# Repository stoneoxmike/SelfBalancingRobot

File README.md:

Self Balancing Robot
To this point, we have stolen EVERYTHING

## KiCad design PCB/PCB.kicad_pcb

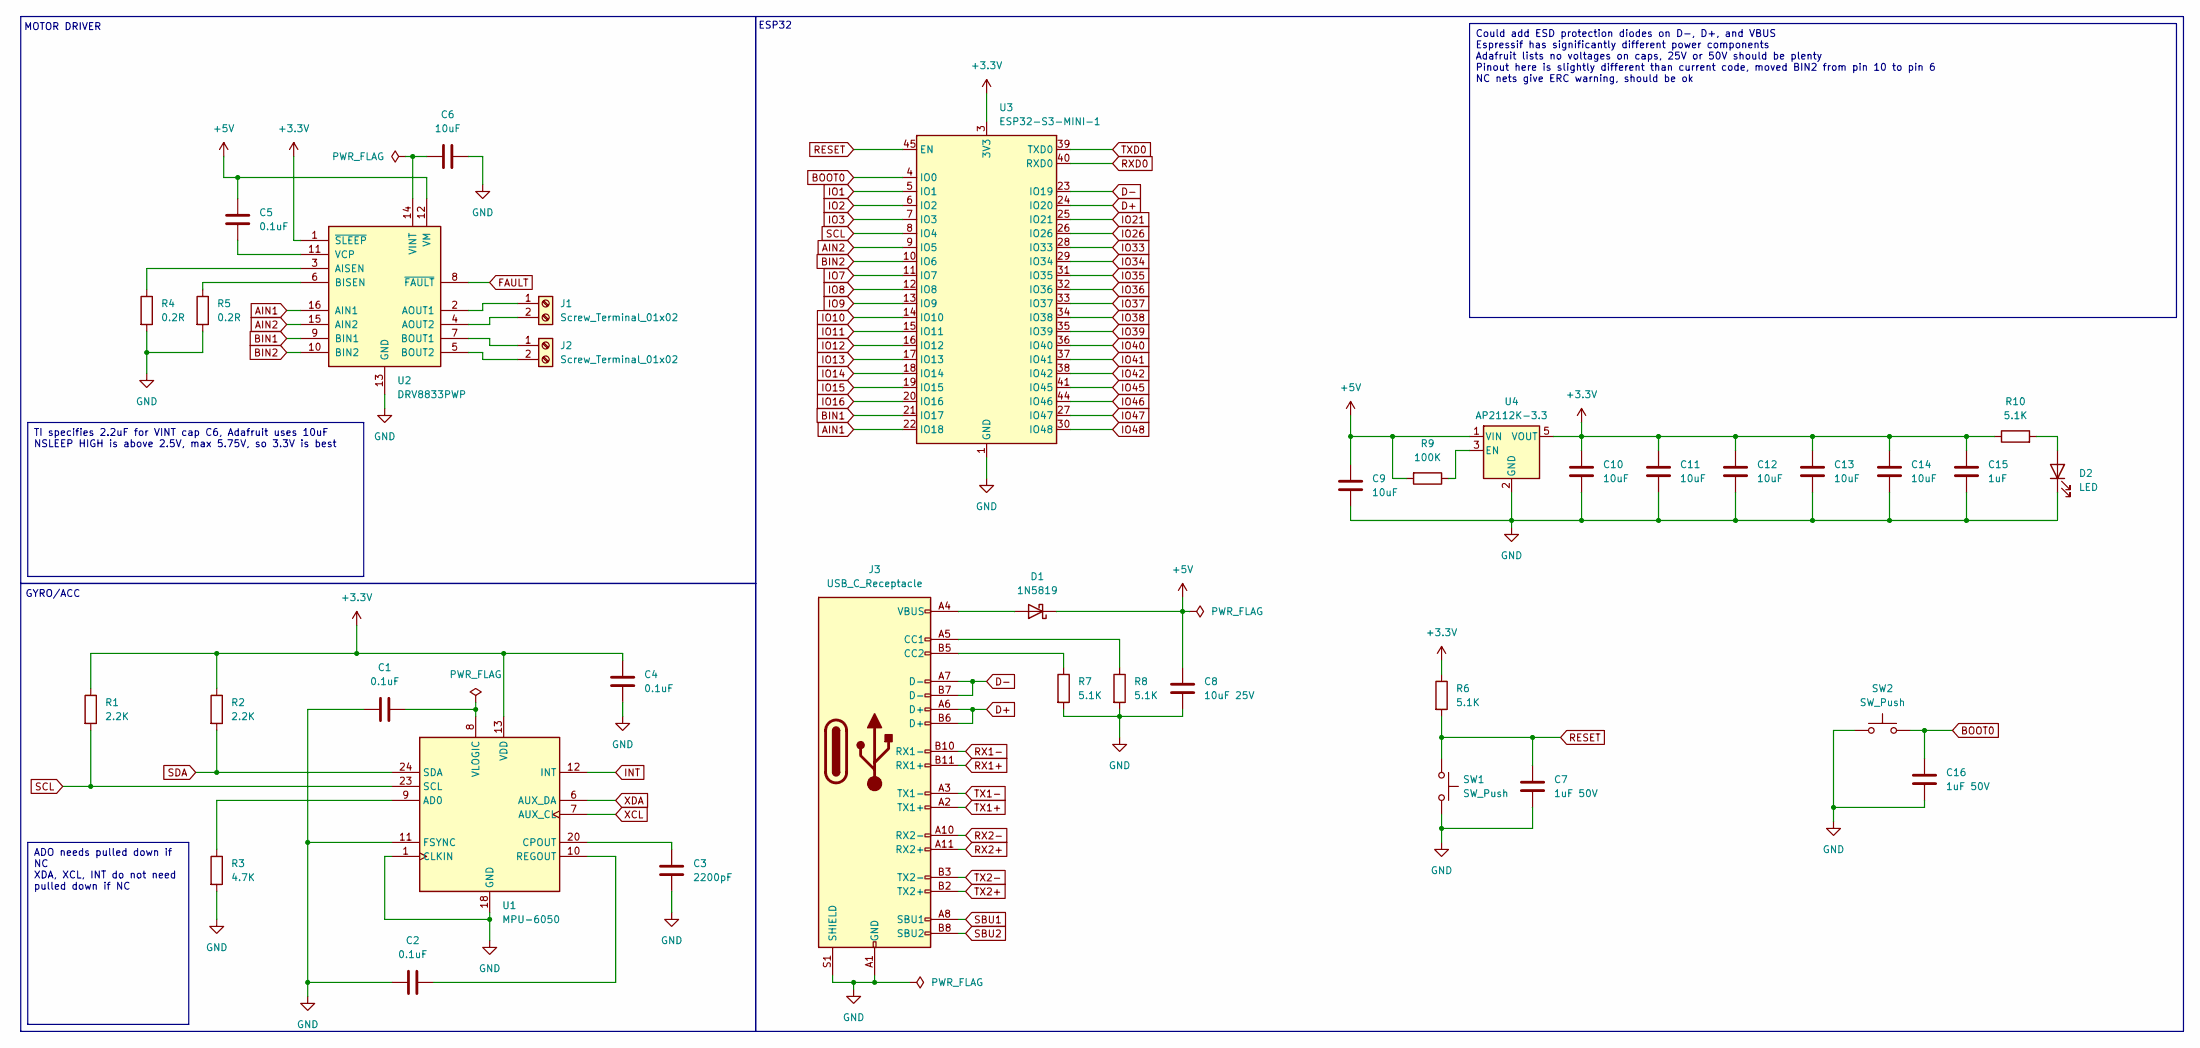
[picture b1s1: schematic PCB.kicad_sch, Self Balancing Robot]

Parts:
C1, C2, C4, C5: 0.1uF; C_0805_2012Metric
C3: 2200pF; C_0805_2012Metric
C6, C9, C10, C11, C12, C13, C14: 10uF; C_0805_2012Metric
C7, C16: 1uF 50V; C_0805_2012Metric
C8: 10uF 25V; C_0805_2012Metric
C15: 1uF; C_0805_2012Metric
D1: 1N5819; D_DO-41_SOD81_P10.16mm_Horizontal
D2: LED; LED_0805_2012Metric
J1: Screw_Terminal_01x02; PinSocket_1x02_P2.54mm_Vertical
J2: Screw_Terminal_01x02; PinHeader_1x02_P2.54mm_Vertical
J3: USB_C_Receptacle; USB_C_Receptacle_Amphenol_12401610E4-2A
R1, R2: 2.2K; R_0805_2012Metric
R3: 4.7K; R_0805_2012Metric
R4, R5: 0.2R; R_0805_2012Metric
R6, R7, R8, R10: 5.1K; R_0805_2012Metric
R9: 100K; R_0805_2012Metric
SW1, SW2: SW_Push; SW_SPST_EVPBF
U1: MPU-6050; InvenSense_QFN-24_4x4mm_P0.5mm
U2: DRV8833PWP; HTSSOP-16-1EP_4.4x5mm_P0.65mm_EP3.4x5mm_Mask2.46x2.31mm_The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
U3: ESP32-S3-MINI-1; ESP32-S2-MINI-1
U4: AP2112K-3.3; SOT-23-5

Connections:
+3.3V: C4.1, C10.1, C11.1, C12.1, C13.1, C14.1, C15.1, R1.1, R2.1, R6.1, R10.1, U1.13 (VDD), U2.1 (~SLEEP), U3.3 (3V3), U4.5 (VOUT)
+5V: C5.1, C8.1, C9.1, D1.1 (K), R9.2, U2.12 (VM), U4.1 (VIN)
AIN1: U2.16 (AIN1), U3.22 (IO18)
AIN2: U2.15 (AIN2), U3.9 (IO5)
BIN1: U2.9 (BIN1), U3.21 (IO17)
BIN2: U2.10 (BIN2), U3.10 (IO6)
BOOT0: C16.1, SW2.2, U3.4 (IO0); also elsewhere on the board
D+: J3.A6 (D+), J3.B6 (D+), U3.24 (IO20)
D-: J3.A7 (D-), J3.B7 (D-), U3.23 (IO19)
FAULT: U2.8 (~FAULT)
GND: C1.2, C2.2, C3.2, C4.2, C6.1, C7.2, C8.2, C9.2, C10.2, C11.2, C12.2, C13.2, C14.2, C15.2, C16.2, D2.1 (K), J3.A1 (GND), J3.A12 (GND), J3.B1 (GND), J3.B12 (GND), J3.S1 (SHIELD), R3.2, R4.2, R5.2, R7.2, R8.2, SW1.2, SW2.1, U1.1 (CLKIN), U1.11 (FSYNC), U1.18 (GND), U2.13 (GND), U2.17 (GND), U3.1 (GND), U3.2 (GND), U3.42 (GND), U3.43 (GND), U3.46 (GND), U3.47 (GND), U3.48 (GND), U3.49 (GND), U3.50 (GND), U3.51 (GND), U3.52 (GND), U3.53 (GND), U3.54 (GND), U3.55 (GND), U3.56 (GND), U3.57 (GND), U3.58 (GND), U3.59 (GND), U3.60 (GND), U3.61 (GND), U3.62 (GND), U3.63 (GND), U3.64 (GND), U3.65 (GND), U4.2 (GND); also elsewhere on the board
INT: U1.12 (INT)
IO1: U3.5 (IO1)
IO2: U3.6 (IO2)
IO3: U3.7 (IO3)
IO7: U3.11 (IO7)
IO8: U3.12 (IO8)
IO9: U3.13 (IO9)
IO10: U3.14 (IO10)
IO11: U3.15 (IO11)
IO12: U3.16 (IO12)
IO13: U3.17 (IO13)
IO14: U3.18 (IO14)
IO15: U3.19 (IO15)
IO16: U3.20 (IO16)
IO21: U3.25 (IO21)
IO26: U3.26 (IO26)
IO33: U3.28 (IO33)
IO34: U3.29 (IO34)
IO35: U3.31 (IO35)
IO36: U3.32 (IO36)
IO37: U3.33 (IO37)
IO38: U3.34 (IO38)
IO39: U3.35 (IO39)
IO40: U3.36 (IO40)
IO41: U3.37 (IO41)
IO42: U3.38 (IO42)
IO45: U3.41 (IO45)
IO46: U3.44 (IO46)
IO47: U3.27 (IO47)
IO48: U3.30 (IO48)
unnamed: D2.2 (A), R10.2
unnamed: J1.1, U2.2 (AOUT1)
unnamed: J1.2, U2.4 (AOUT2)
unnamed: J2.1, U2.7 (BOUT1)
unnamed: J2.2, U2.5 (BOUT2)
unnamed: J3.B5 (CC2), R7.1
unnamed: R3.1, U1.9 (AD0)
unnamed: C3.1, U1.20 (CPOUT)
unnamed: C2.1, U1.10 (REGOUT)
unnamed: C1.1, U1.8 (VLOGIC)
unnamed: R4.1, U2.3 (AISEN)
unnamed: R5.1, U2.6 (BISEN)
unnamed: C5.2, U2.11 (VCP)
unnamed: C6.2, U2.14 (VINT)
unnamed: R9.1, U4.3 (EN)
RESET: C7.1, R6.2, SW1.1, U3.45 (EN); also elsewhere on the board
RX1+: J3.B11 (RX1+)
RX1-: J3.B10 (RX1-)
RX2+: J3.A11 (RX2+)
RX2-: J3.A10 (RX2-)
RXD0: U3.40 (RXD0)
SBU1: J3.A8 (SBU1)
SBU2: J3.B8 (SBU2)
SCL: R1.2, U1.23 (SCL), U3.8 (IO4)
SDA: R2.2, U1.24 (SDA)
TX1+: J3.A2 (TX1+)
TX1-: J3.A3 (TX1-)
TX2+: J3.B2 (TX2+)
TX2-: J3.B3 (TX2-)
TXD0: U3.39 (TXD0)
XCL: U1.7 (AUX_CL)
XDA: U1.6 (AUX_DA)

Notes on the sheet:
TI specifies 2.2uF for VINT cap C6, Adafruit uses 10uF NSLEEP HIGH is above 2.5V, max 5.75V, so 3.3V is best
Could add ESD protection diodes on D-, D+, and VBUS Espressif has significantly different power components Adafruit lists no voltages on caps, 25V or 50V should be plenty Pinout here is slightly different than current code, moved BIN2 from pin 10 to pin 6 NC nets give ERC warning, should be ok
ADO needs pulled down if NC XDA, XCL, INT do not need pulled down if NC
GYRO/ACC
MOTOR DRIVER
ESP32

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
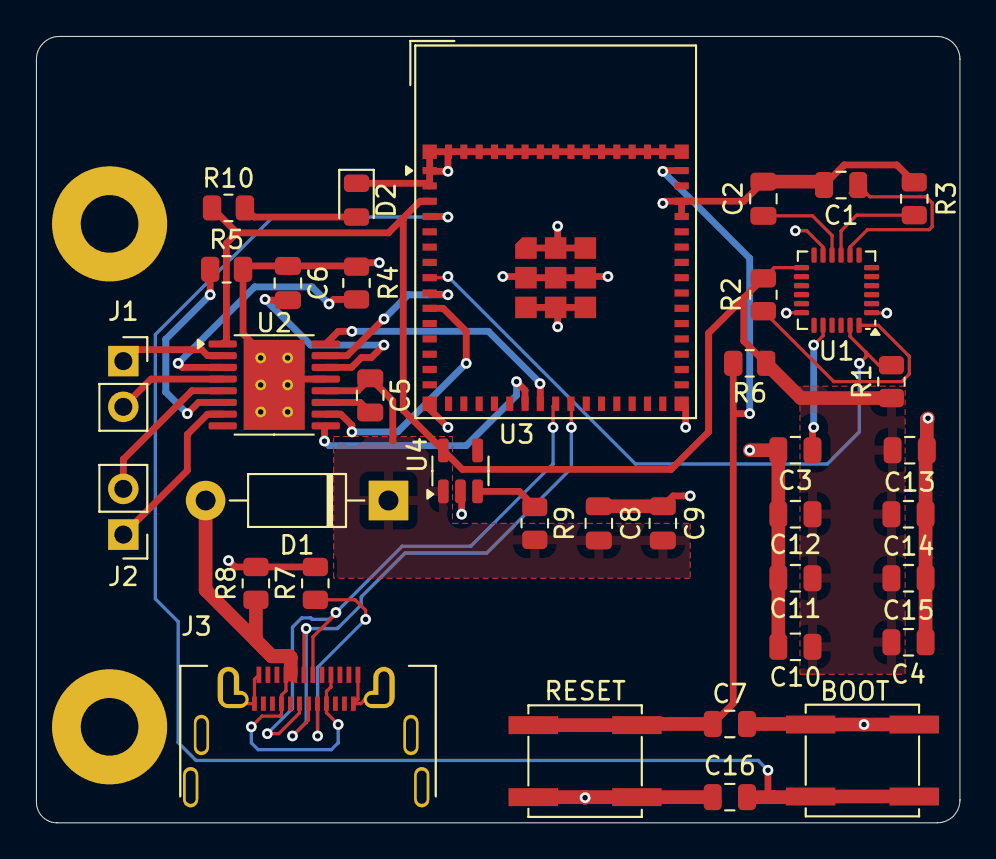
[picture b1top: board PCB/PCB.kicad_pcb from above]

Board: 2 copper layers, 51.3 x 43.7 mm, 38 parts (0 on the bottom side), 29 nets.

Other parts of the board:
BOOT: SW_Push; SW_SPST_EVPBF
GND: MountingHole_3.2mm_M3_Pad
RESET: SW_Push; SW_SPST_EVPBF

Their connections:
BOOT0: BOOT.2; also elsewhere on the board
GND: BOOT.1, GND.1, RESET.2; also elsewhere on the board
RESET: RESET.1; also elsewhere on the board

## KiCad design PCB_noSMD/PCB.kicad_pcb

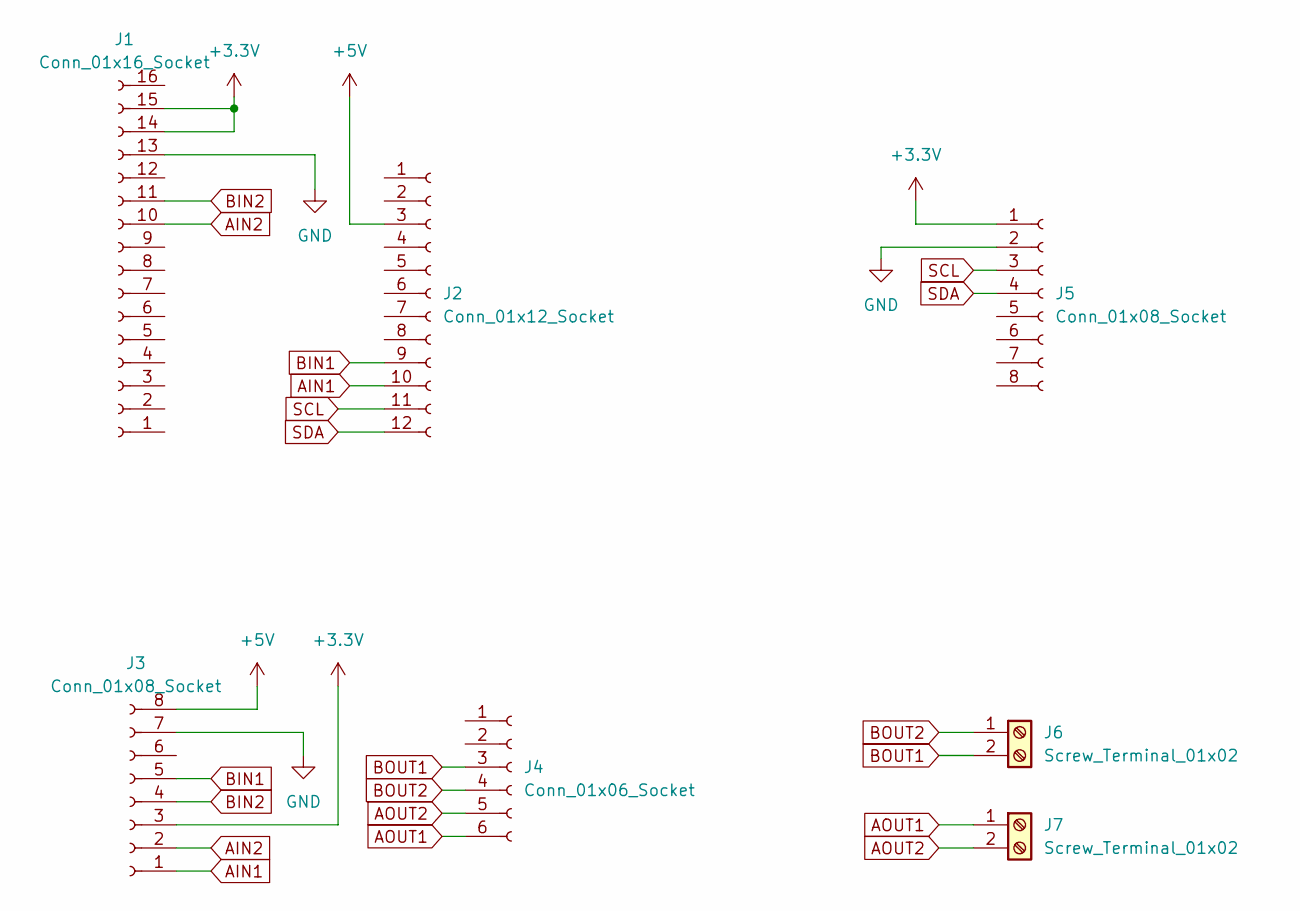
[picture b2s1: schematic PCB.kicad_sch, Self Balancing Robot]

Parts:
J1: Conn_01x16_Socket; PinHeader_1x16_P2.54mm_Vertical
J2: Conn_01x12_Socket; PinHeader_1x12_P2.54mm_Vertical
J3, J5: Conn_01x08_Socket; PinHeader_1x08_P2.54mm_Vertical
J4: Conn_01x06_Socket; PinHeader_1x06_P2.54mm_Vertical
J6, J7: Screw_Terminal_01x02; PinHeader_1x02_P2.54mm_Vertical

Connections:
+3.3V: J1.14, J1.15, J3.3, J5.1
+5V: J2.3, J3.8
AIN1: J2.10, J3.1
AIN2: J1.10, J3.2
AOUT1: J4.6, J7.1
AOUT2: J4.5, J7.2
BIN1: J2.9, J3.5
BIN2: J1.11, J3.4
BOUT1: J4.3, J6.2
BOUT2: J4.4, J6.1
GND: J1.13, J3.7, J5.2
SCL: J2.11, J5.3
SDA: J2.12, J5.4

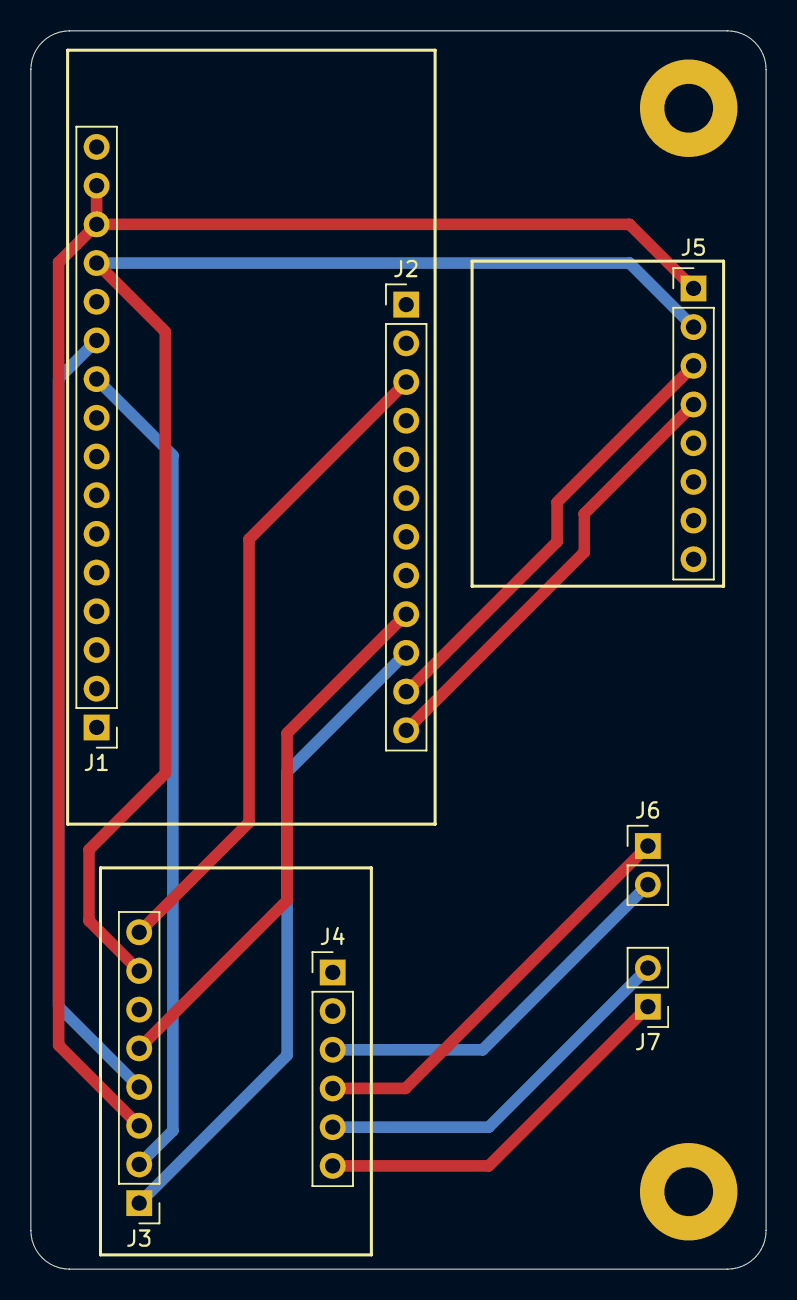
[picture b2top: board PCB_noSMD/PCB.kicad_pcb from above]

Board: 2 copper layers, 48.3 x 81.3 mm, 7 parts (0 on the bottom side), 13 nets.

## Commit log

2024-06-05 add gitignore for PCB
2024-06-05 Create PCB Project
2024-06-05 Add PCB_mutex
2024-06-10 PCB Mutex
2024-06-10 update to PIO
2024-06-10 add dependencies
2024-06-12 Update ISR for ESP32
2024-06-12 Switch from .ino to .cpp
2024-06-12 Fix ISR math for 240MHz
2024-06-13 Remove Ultrasonic Sensor Code
2024-06-13 Update Motor Driver Pinout
2024-06-13 Fix Motor Driver pins again
2024-06-17 Make motor outputs analog, motors working, extra test program created
2024-06-18 PCB Progress
2024-06-19 PCB work, finished schematic Rev A
2024-06-19 Progress, gyro working with new library
2024-06-19 Worked on test code
2024-07-01 progress?
2024-07-03 Added footprints and nets to PCB file, set up design rules
2024-07-03 Motors moving according to accel/gyro without ISR
2024-07-04 Finished routing header only PCB
2024-07-09 Comments + PCB work
2024-07-09 Finished 2nd PCB
2024-07-10 Finished second PCB
2024-07-10 Progress, working on angle
2024-07-15 updated PID parameters (close not perfect)
2024-07-17 calculate calibration values for MPU6050
2024-07-29 PCB changes
2024-07-29 Swapped gyro directions to account for different mounting orientation
2024-07-29 Progress, PCB working
2024-07-31 adjust calibration values
2024-07-31 adjust calibration script
2024-07-31 Updated PID constants, need to tune Kd
2024-08-05 Progress, PID looking pretty nice for video
2024-08-05 Update target angle for taped battery
